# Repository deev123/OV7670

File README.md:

# OV7670 Library for the RP2040 Raspberry Pi Pico

## Preface

The OV7670 is a bare-bones CMOS camera sensor module with a SCCB interface for registers setting the sensor settings and 8 data pins which stream half pixels in a VGA like way with a HSync and VSyc deliniating frames.
There is a version of the sensor with a buffer but this repo does not use it. Instead it uses the Pico to capture and store the image data.

<a href="https://amzn.eu/d/2ike6i4">OV7670 sensor on Amazon</a>

## Repo
This repo includes:
- C firmware source code for the OV7670 camera sensor module and Raspberry Pi Pico RP2040
- A Web application for interfacing with it (which reads serial via a separate server)
- A Python serial server which is used by the web application to communicate with the sensor

Lib and Src contain the firmware

The 'Terminal' directory contains the web application for visualising data from and sending data to the camera, as well as the python 
server which should be run locally to allow the website access to a serial port

## Pin Configuration:

The pin wiring of D0-D7 allows for the most efficient reading of the bits for reading the half pixel bytes:

| OV7670 Pin | PICO Pin |
| - | - |
| 3.3V | 3V3(OUT) |
| RET | 3V3(OUT) |
| DGND | GND |
| PWDN | GND |
| SDA | GP0 |
| SCL | GP1 |
| XLK | GP21 |
| VS | GP6 |
| HS | GP5 |
| PLK | GP7 |
| D0 | GP8 |
| D1 | GP9 |
| D2 | GP10 |
| D3 | GP11 |
| D4 | GP12 |
| D5 | GP13 |
| D6 | GP14 |
| D7 | GP15 |

## PCB

I designed a double sided PCB in KiCAD to fit the OV7670 and Pico.
The lines are length matched (hence the sqiggly traces) making it suitable for high frequency reading when I can get it to work.

There are optional pullup resistors on the I2C SDA and SCL lines but the internal ones seem to be sufficient.

There is also space for an additional female header to access spare pins to connect with something else.

I got the PCB printed from <a href="https://jlcpcb.com">JLC PCB</a>

## Web Terminal

You can paste data copied from a terminal like putty or teraterm into a box for it to render

You need to have the image width set up right at least for correct rendering of rows and the height should be set to fit the image

There is also an option for big or little endian interpretation of the pixels (which are 2 bytes RGB565)

Or listen to the serial. For this you need to have the Flask server to read the serial port.

The Pico has limited memory and since I am not yet using two cores I need to store the pixels before I can transmit them, so at the moment I skip pixels to downscale the image to something that fits in memory

There is some unfinished work:
- I want to utilise both cores of the RP2040 processor so I can capture and trasmit the pixels at the same time in something like a producer consumer pattern. This will allow transmitting a frame of full resolution in one pass
- I need to modify register values to properly set up the camera settings to capture a coloured image
- I need to fix some data integrity issues

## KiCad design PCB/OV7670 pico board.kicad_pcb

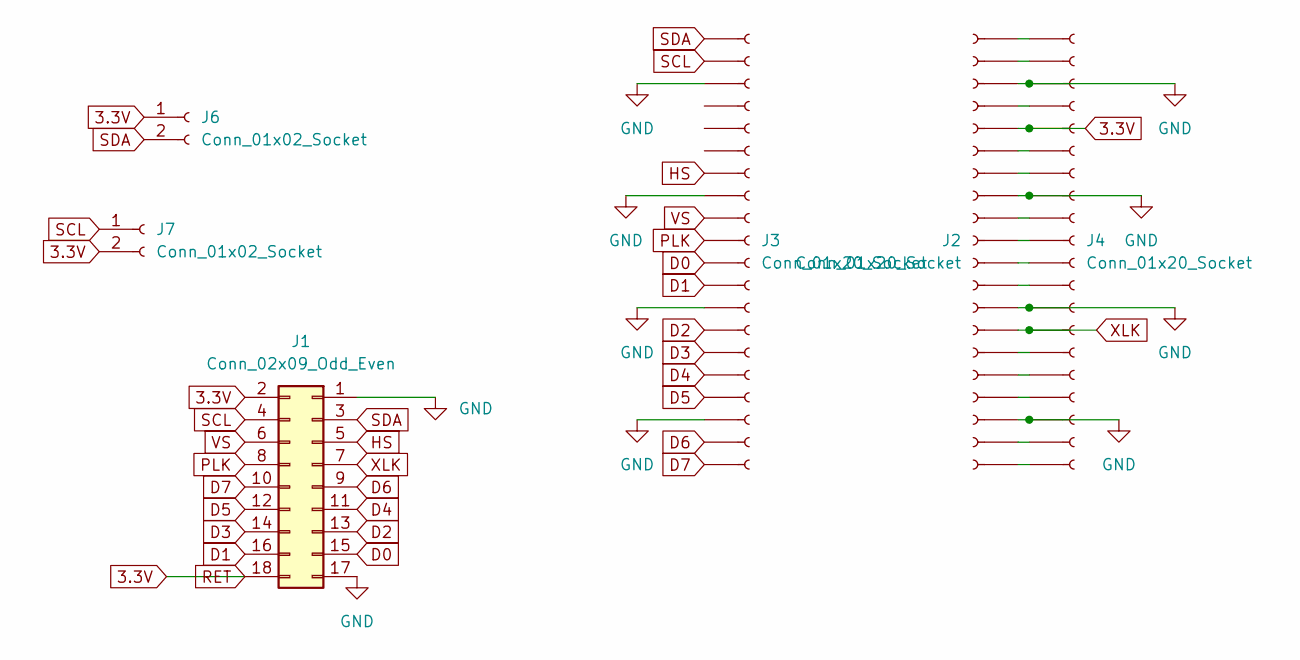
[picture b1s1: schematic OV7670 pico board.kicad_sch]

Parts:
J1: Conn_02x09_Odd_Even; PinSocket_2x09_P2.54mm_Vertical
J2, J3, J4: Conn_01x20_Socket; PinSocket_1x20_P2.54mm_Vertical
J6, J7: Conn_01x02_Socket; PinSocket_1x02_P2.54mm_Vertical

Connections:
3.3V: J1.2, J1.18, J2.5, J4.5, J6.1, J7.2
D0: J1.15, J3.11
D1: J1.16, J3.12
D2: J1.13, J3.14
D3: J1.14, J3.15
D4: J1.11, J3.16
D5: J1.12, J3.17
D6: J1.9, J3.19
D7: J1.10, J3.20
GND: J1.1, J1.17, J2.3, J2.8, J2.13, J2.18, J3.3, J3.8, J3.13, J3.18, J4.3, J4.8, J4.13, J4.18
HS: J1.5, J3.7
unnamed: J2.1, J4.1
unnamed: J2.2, J4.2
unnamed: J2.4, J4.4
unnamed: J2.6, J4.6
unnamed: J2.7, J4.7
unnamed: J2.9, J4.9
unnamed: J2.10, J4.10
unnamed: J2.11, J4.11
unnamed: J2.12, J4.12
unnamed: J2.15, J4.15
unnamed: J2.16, J4.16
unnamed: J2.17, J4.17
unnamed: J2.19, J4.19
unnamed: J2.20, J4.20
PLK: J1.8, J3.10
SCL: J1.4, J3.2, J7.1
SDA: J1.3, J3.1, J6.2
VS: J1.6, J3.9
XLK: J1.7, J2.14, J4.14

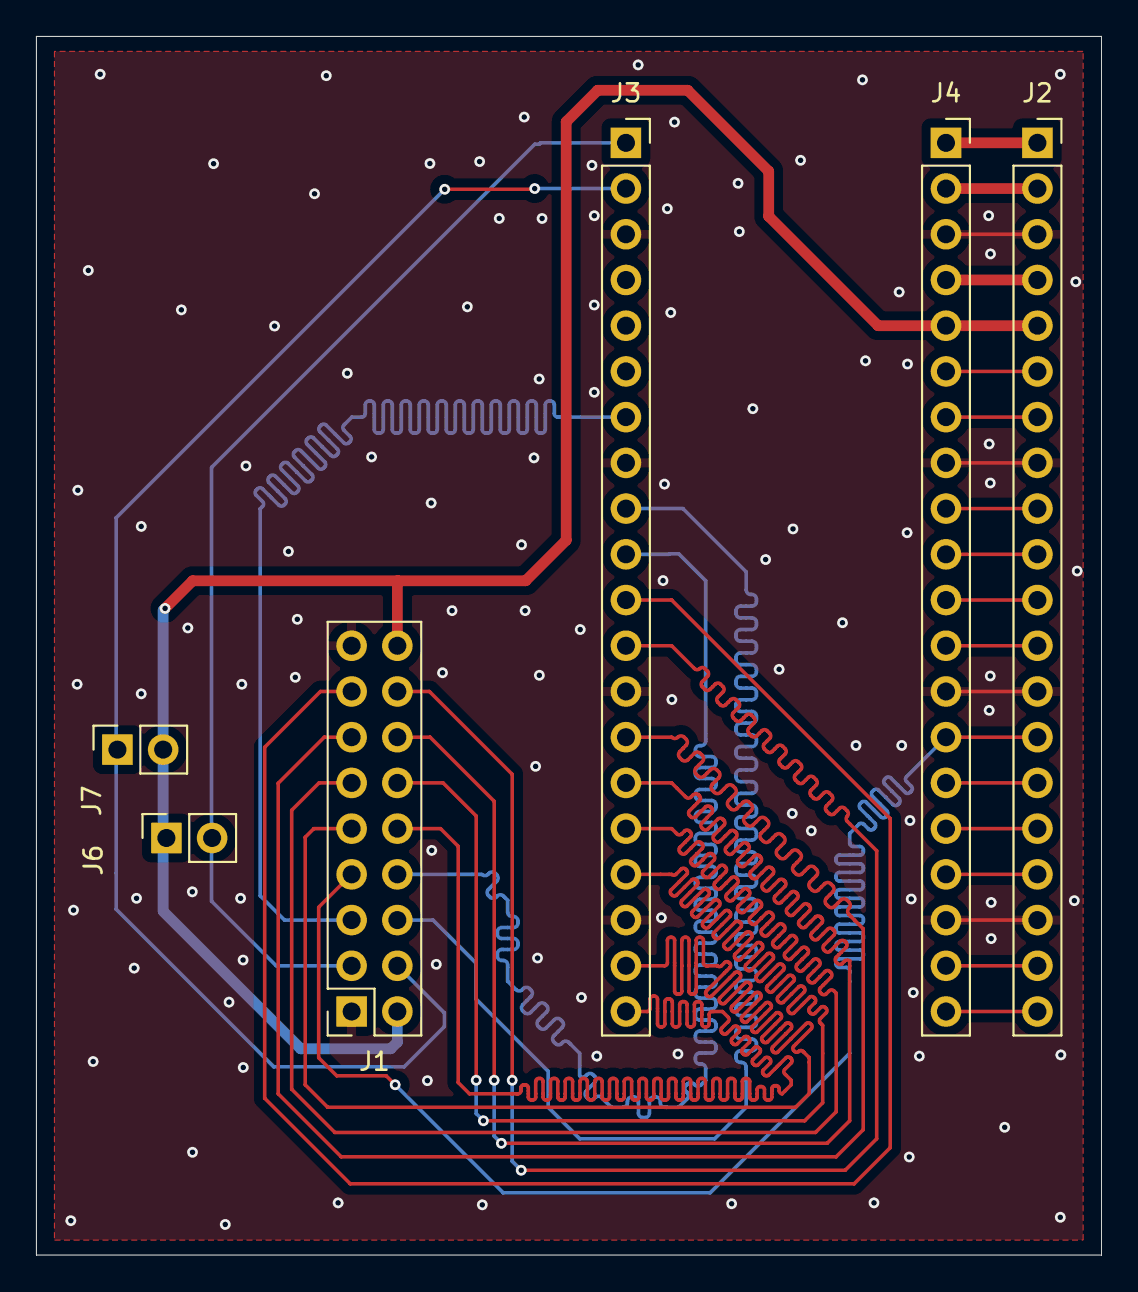
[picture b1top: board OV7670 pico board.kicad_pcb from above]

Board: 2 copper layers, 59.2 x 67.7 mm, 6 parts (0 on the bottom side), 30 nets.

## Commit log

2024-03-30 got the sccb interface to respond to pico i2c comms on address 0x21 (i think thats right). xclk necessary for sccb interface to work
2024-03-30 vsync and pclk seem to be doing something but href seems weird (no configuration with sccb done) TODO: see on a scope
2024-04-01 Writing to register works. Unsure if bit[0] is LSB or MSB. TODO: find out
2024-04-01 refactored into OV7670 library. Bit[7] in datasheet refers to the LSB and bit[0] the MSB for register values as proved by the register resetting bit
2024-04-01 last commit mistakenly said bit[7] was LSB, this was untrue and has been corrected. Current code will set register 0x11, print all values, reset using the reset bit in register 0x12, and read all the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
2024-04-01 removed unnecessary files. Commented out reset registers
2024-04-01 print all register values at start of main
2024-04-02 fixed scaling clock error. vsync is now every 1 second, href every 2ms, plk every 1.28us
2024-04-02 Fix pulse counting loop The problem is that while waiting for href to go low, we were not checking if vsync goes high, meaning it is impossible for the frame to end
2024-04-04 Capture test pattern and print as hex to uart
2024-04-04 Make take a photo. Refactor test pattern generator into a function
2024-04-06 Start on Terminal web page for visualisation of data Terminal will which will visualise images from the camera and eventually render the serial data in real time. Terminal currently has a class which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
2024-04-06 Quickly clean up formatting with CSS
2024-04-06 Add Hex input render feature. Works as intended
2024-04-06 Use floating point scale factors to convert from rgb565 to rgba8888. Still problems with colour blending i think caused by floating point innacuracy
2024-04-06 Fix rgba conversion issue. Unsure what the issue was but i fixed it accidentally by refactoring the conversion into a function
2024-04-06 Make the camera capture whole image with multiple buffers. The code appends to the frame buffer until it has no more space, prints the frame buffer to serial, and then fills the frame buffer with the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
2024-04-13 Terminal/*: Refactor. Improve UI. Add height and width controls Use - names for css and camel case for JavaScript. Refactor rendering code into rendering.js. Add width and height option to UI, Make U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
2024-07-13 main.c: Add initial serial command parser
2024-07-13 refactor command and ring_buf library new ring_buf and command libraries contain the code for processing commands with a single function and defining a ring buffer data structure the old code has bee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
2024-07-13 Handle backspaces, substitute special chars Backspaces now result in going back in the command buffer and special characters are printed in a more user friendly way
2024-07-13 command: Add AT - OK command
2024-07-15 Implement AT SETREG GETREG and PIC commands AT will respond with OK if it was received SETREG <reg> <value> sets register <reg> to <value> and responds with the value of register <reg> GETREG <reg> r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
2024-07-15 Create Serial Server and command terminal dev page SerialServer.py is ran with a --port argument (COM4 by default). It then takes get and post requests to interface between a client and the camera se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
2024-07-15 index.html: Change styles for index page
2024-07-16 lib/command.c: Clean up extra printfs from responses
2024-07-16 Terminal/*: Add serial terminal to index.html The serial terminal can now send commands and display the response
2024-07-17 All: Change comms, Add buttons to site. Add logs to server Camera now sends packets as raw bytes instead of hex and transmissions begin with a size and no longer end in \r. \r is now only for command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
2024-07-18 All: Add start of packet delimiter to camera responses A packet from the camera always begins with bytes for white black red green blue since this long sequence is very unlikely to occur in a transmi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
2024-09-27 Terminal/serial.js: Fixed git tracking error serial.js was being excluded
2024-09-28 Update README.md
    Fix SCL and SDA incorrect GPIO number
2025-06-09 fix colour bar generation command
2025-06-09 add KiCAD PCB project and outputs
2025-06-23 Add gitignore
2025-06-23 fix error in gitignore
